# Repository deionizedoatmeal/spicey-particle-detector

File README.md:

# spicey-particle-detector
Cribbing off the MightyOhm geiger counter, developing a RP2040 based geiger counter.

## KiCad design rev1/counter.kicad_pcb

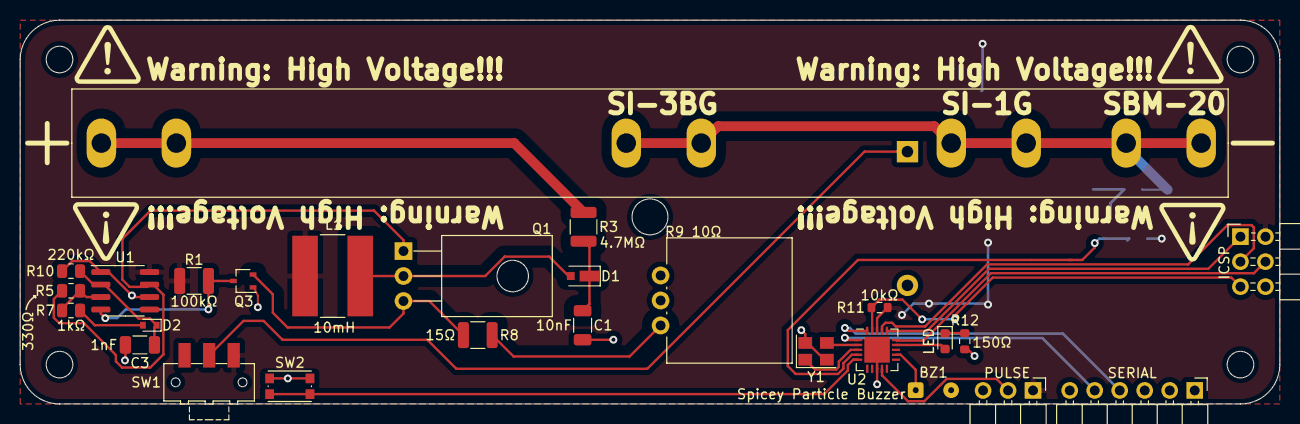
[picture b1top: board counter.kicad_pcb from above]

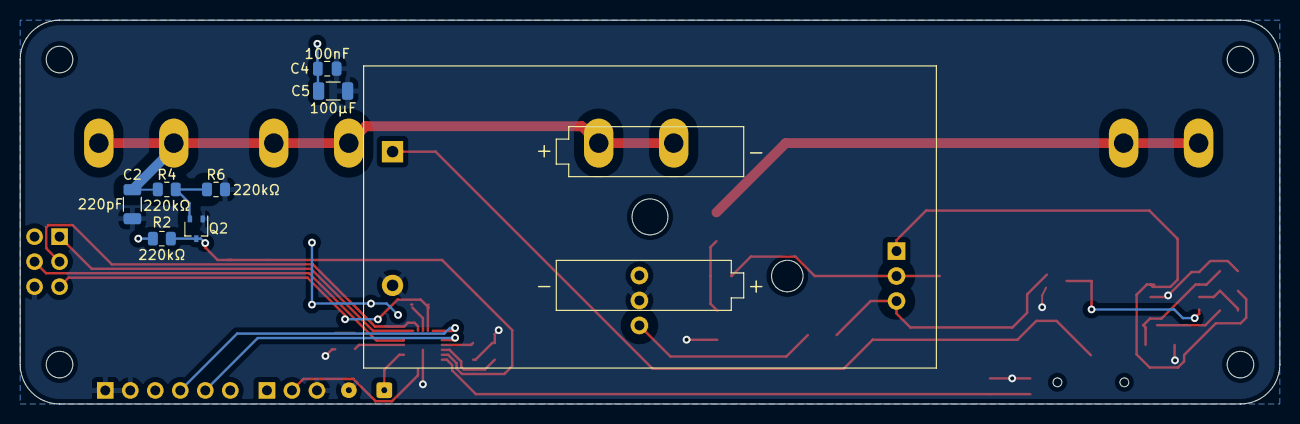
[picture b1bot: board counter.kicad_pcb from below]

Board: 2 copper layers, 128.0 x 39.0 mm, 39 parts (8 on the bottom side), 29 nets.

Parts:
BT1: Battery; BatteryHolder_MPD_BC2AAPC_2xAA
BZ1: Spicey Particle Buzzer; SolderWire-0.1sqmm_1x02_P3.6mm_D0.4mm_OD1mm
C1: 10nF; C_1206_3216Metric
C2: 220pF; C_1206_3216Metric
C3: 1nF; C_1206_3216Metric
C4: 100nF; C_0805_2012Metric
C5: 100μF; C_1206_3216Metric
D1: MSQ1PJHM3/H; D_DO-219AD
D2: 1N4148WT; D_SOD-523
D3: LED; LED_0603_1608Metric
H1, H2, H3, H4: MountingHole; MountingHole_2.7mm_M2.5
ICSP: Conn_02x03_Odd_Even; PinHeader_2x03_P2.54mm_Horizontal
L1: 10mH; L_Bourns-SRN8040_8x8.15mm
PULSE: Conn_01x03; PinHeader_1x03_P2.54mm_Horizontal
Q1: KSE13003H2ASTU; TO-126-3_Horizontal_TabDown
Q2, Q3: BC816-16WF; SOT-323_SC-70
R1: 100kΩ; R_1210_3225Metric
R2, R4, R6, R10: 220kΩ; R_0805_2012Metric
R3: 4.7MΩ; R_1210_3225Metric
R5: 330Ω; R_0805_2012Metric
R7: 1kΩ; R_0805_2012Metric
R8: 15Ω; R_1210_3225Metric
R9: 10Ω; Potentiometer_Vishay_148-149_Single_Vertical
R11: 10kΩ; R_0603_1608Metric
R12: 150Ω; R_0603_1608Metric
SERIAL: Conn_01x06; PinHeader_1x06_P2.54mm_Horizontal
SW1: SW_Push_SPDT; SW_SPDT_CK-JS102011SAQN
SW2: SW_Push; SW_Push_1P1T_NO_CK_KMR2
U1: TLC555xD; SOIC-8_3.9x4.9mm_P1.27mm
U2: ATtiny2313-20M; MLF-20-1EP_4x4mm_P0.5mm_EP2.6x2.6mm
V1: Nuclear-Radiation_Detector; Geiger–Müller_tube
Y1: ECS-80-12-33-JGN; Crystal_SMD_3225-4Pin_3.2x2.5mm

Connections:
/BAT: BT1.1 (+), SW1.2 (B)
/GM+: R3.2, V1.1
/GM-: C2.1, R4.1, V1.2
/GM_CATH: C1.1, D1.1 (K), R3.1
/GM_PULSE: Q2.3 (C), R2.2, U2.4 (PD2)
/HV_COLLECTOR: D1.2 (A), L1.2, Q1.2 (C)
/HV_EMMITTER: Q1.3 (E), Q3.2 (B), R8.1
/HV_R: R8.2, R9.1
/LED: D3.2 (A), U2.14 (PB4)
/PB5: ICSP.4, U2.15 (PB5)
/PB6: ICSP.1, U2.16 (PB6)
/PB7: ICSP.3, U2.17 (PB7)
/PD0: SERIAL.4, U2.20 (PD0)
/PD1: SERIAL.5, U2.1 (PD1)
/PD6: PULSE.2, U2.9 (PD6)
/PIEZO: BZ1.1 (-), U2.12 (PB2)
/PULSE_BASE: Q2.2 (B), R4.2, R6.1
/X1: U2.3 (PA0/XTAL1), Y1.1
/X2: U2.2 (PA1/XTAL2), Y1.3
/~RESET: ICSP.5, R11.2, U2.19 (PA2/~RESET)
GND: BT1.2 (-), BZ1.2 (+), C1.2, C2.2, C3.2, C4.2, C5.2, ICSP.6, PULSE.3, Q2.1 (E), Q3.1 (E), R6.2, R9.2, R10.2, R12.2, SERIAL.1, SERIAL.2, SW2.2, U1.1 (GND), U1.6 (THR), U2.8 (GND), U2.21 (GND), Y1.2, Y1.4
unnamed: C3.1, D2.1 (K), R10.1, U1.2 (TR)
unnamed: D2.2 (A), R7.2
unnamed: D3.1 (K), R12.1
unnamed: Q1.1 (B), R5.2, U1.7 (DIS)
unnamed: Q3.3 (C), R1.2, U1.4 (R)
unnamed: R5.1, R7.1, U1.3 (Q)
unnamed: SW2.1, U2.5 (PD3)
VCC: C4.1, C5.1, ICSP.2, L1.1, PULSE.1, R1.1, R2.1, R11.1, SW1.3 (C), U1.8 (VCC), U2.18 (VCC)

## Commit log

2022-06-12 inital rev of mightyohm based board
